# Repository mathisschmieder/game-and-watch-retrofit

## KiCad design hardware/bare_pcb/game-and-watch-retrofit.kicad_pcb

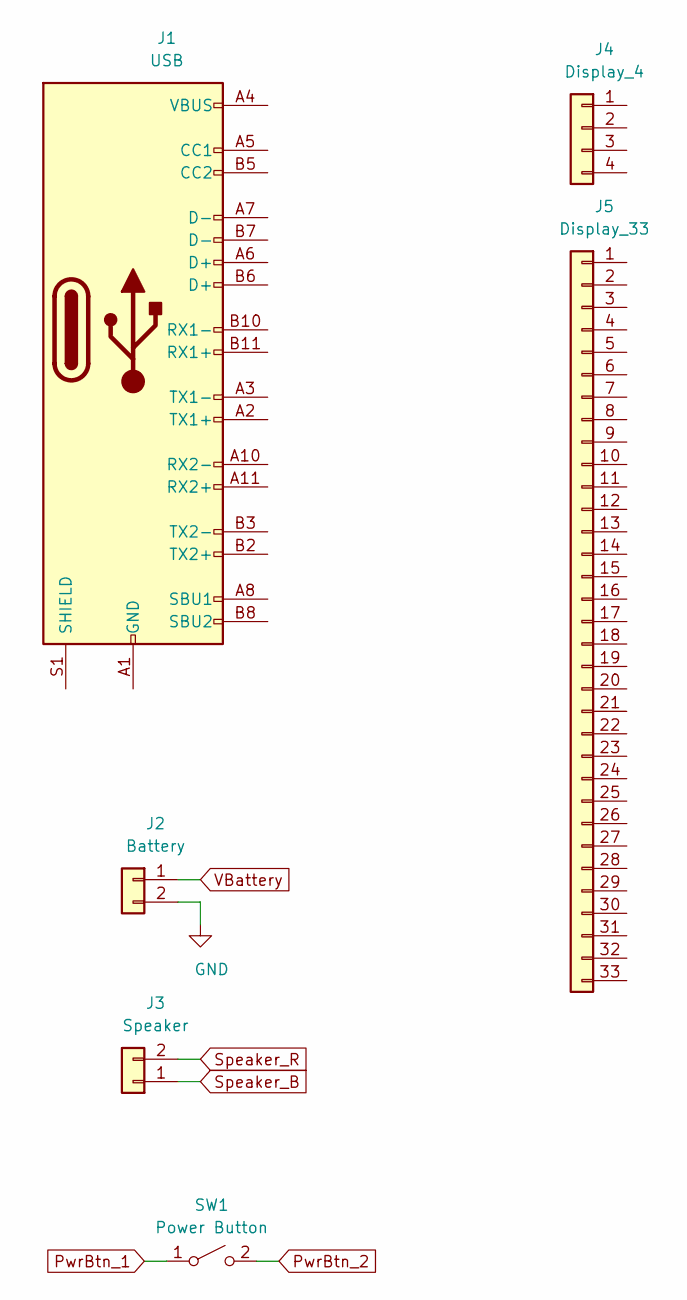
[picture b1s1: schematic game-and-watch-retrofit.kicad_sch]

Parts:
J1: USB; DX07BN24JA2R1300
J2: Battery; Molex-78171-0002-0
J3: Speaker; GaW-Speaker
J4: Display_4; 2328702-4
J5: Display_33; Molex-502078-3310-Manufacturer_Recommended
SW1: Power Button; SKSLLAE010

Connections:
GND: J2.2
unnamed: J1.A1 (GND), J1.A12 (GND), J1.B1 (GND), J1.B12 (GND)
unnamed: J1.A4 (VBUS), J1.A9 (VBUS), J1.B4 (VBUS), J1.B9 (VBUS)
PwrBtn_1: SW1.1 (A)
PwrBtn_2: SW1.2 (B)
Speaker_B: J3.1
Speaker_R: J3.2
VBattery: J2.1

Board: 4 copper layers, 6 parts (0 on the bottom side), 2 nets, no tracks yet.

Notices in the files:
parts and their libraries:
Copyright 2016 Accelerated Designs. All rights reserved.
